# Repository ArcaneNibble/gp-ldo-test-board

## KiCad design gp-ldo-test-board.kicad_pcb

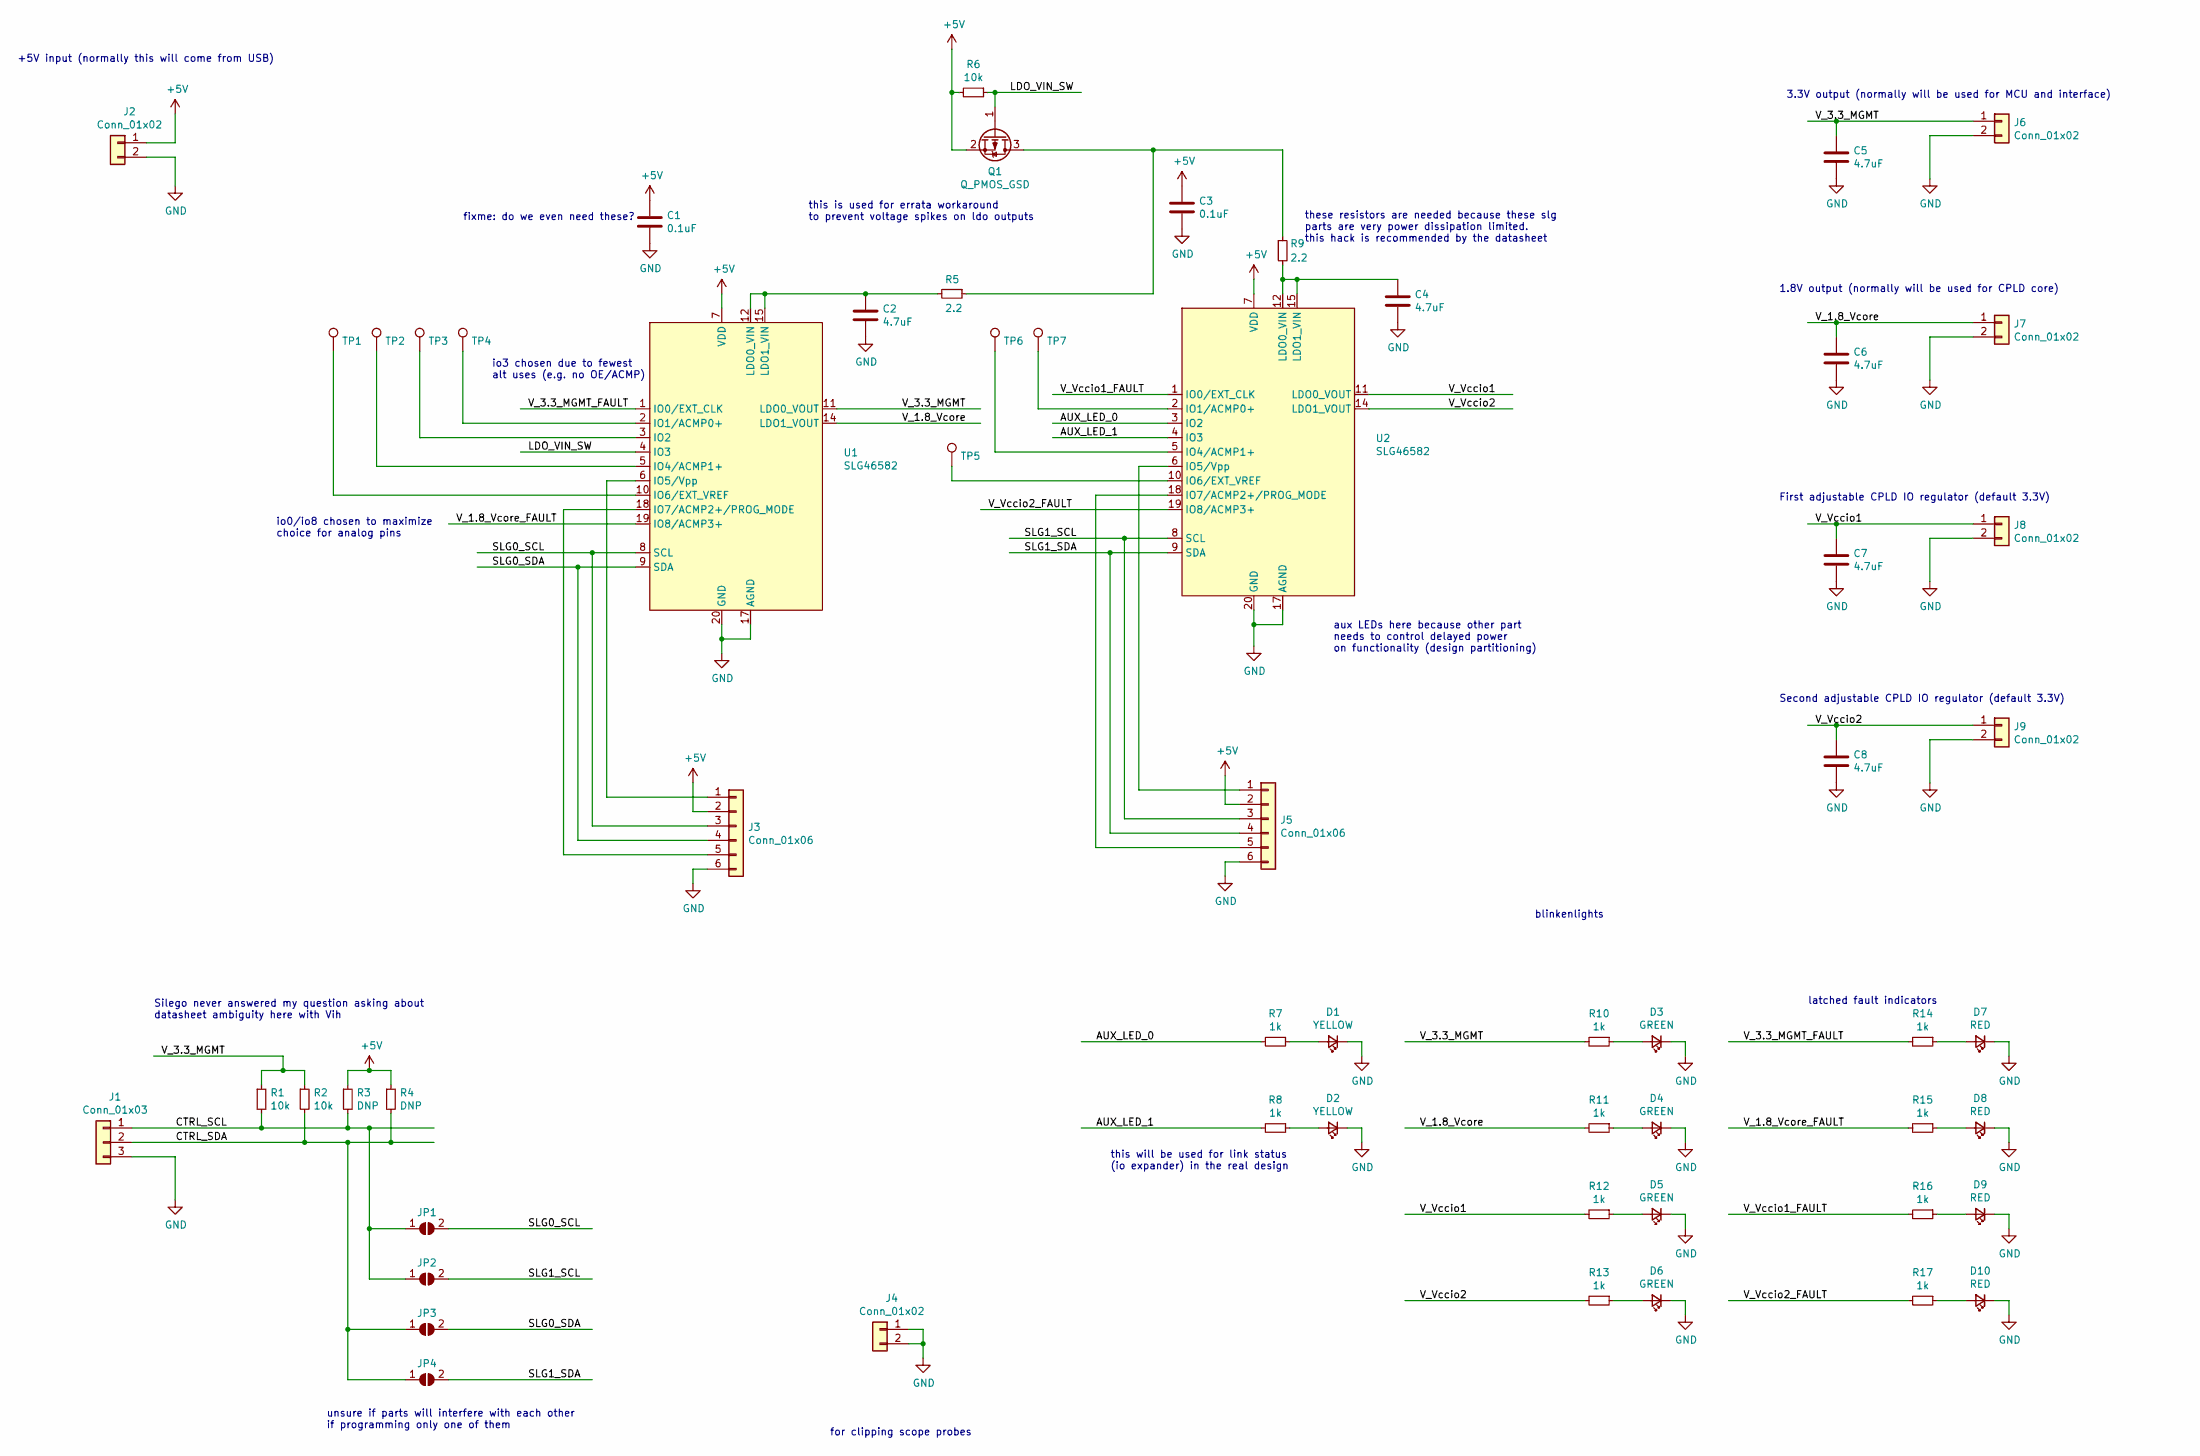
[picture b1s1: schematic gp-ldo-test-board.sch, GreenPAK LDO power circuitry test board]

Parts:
C1, C3: 0.1uF; C_0402_1005Metric
C2, C4, C5, C6, C7, C8: 4.7uF; C_0805_2012Metric
D1, D2: YELLOW; LED_0805_2012Metric
D3, D4, D5, D6: GREEN; LED_0805_2012Metric
D7, D8, D9, D10: RED; LED_0805_2012Metric
J1: Conn_01x03; PinHeader_1x03_P2.54mm_Vertical
J2, J4, J6, J7, J8, J9: Conn_01x02; PinHeader_1x02_P2.54mm_Vertical
J3, J5: Conn_01x06; PinHeader_1x06_P2.54mm_Vertical
JP1, JP2, JP3, JP4: SolderJumper_2_Open; SolderJumper-2_P1.3mm_Open_Pad1.0x1.5mm
Q1: Q_PMOS_GSD; SOT-23
R1, R2, R6: 10k; R_0402_1005Metric
R3, R4: DNP; R_0402_1005Metric
R5, R9: 2.2; R_0402_1005Metric
R7, R8, R10, R11, R12, R13, R14, R15, R16, R17: 1k; R_0402_1005Metric
TP1, TP2, TP3, TP4, TP5, TP6, TP7: TestPoint; TestPoint_Pad_1.0x1.0mm
U1, U2: SLG46582; SLG46580

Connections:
+5V: C1.1, C3.1, J2.1, J3.2, J5.2, Q1.2 (S), R3.1, R4.1, R6.2, U1.7 (VDD), U2.7 (VDD)
/AUX_LED_0: R7.2, U2.3 (IO2)
/AUX_LED_1: R8.2, U2.4 (IO3)
/CTRL_SCL: J1.1, JP1.1 (A), JP2.1 (A), R1.2, R3.2
/CTRL_SDA: J1.2, JP3.1 (A), JP4.1 (A), R2.2, R4.2
/LDO_VIN_SW: Q1.1 (G), R6.1, U1.4 (IO3)
/SLG0_SCL: J3.3, JP1.2 (B), U1.8 (SCL)
/SLG0_SDA: J3.4, JP3.2 (B), U1.9 (SDA)
/SLG1_SCL: J5.3, JP2.2 (B), U2.8 (SCL)
/SLG1_SDA: J5.4, JP4.2 (B), U2.9 (SDA)
/V_1.8_Vcore: C6.1, J7.1, R11.2, U1.14 (LDO1_VOUT), U1.16 (LDO1_VOUT)
/V_1.8_Vcore_FAULT: R15.2, U1.19 (IO8/ACMP3+)
/V_3.3_MGMT: C5.1, J6.1, R1.1, R2.1, R10.2, U1.11 (LDO0_VOUT), U1.13 (LDO0_VOUT)
/V_3.3_MGMT_FAULT: R14.2, U1.1 (IO0/EXT_CLK)
/V_Vccio1: C7.1, J8.1, R12.2, U2.11 (LDO0_VOUT), U2.13 (LDO0_VOUT)
/V_Vccio1_FAULT: R16.2, U2.1 (IO0/EXT_CLK)
/V_Vccio2: C8.1, J9.1, R13.2, U2.14 (LDO1_VOUT), U2.16 (LDO1_VOUT)
/V_Vccio2_FAULT: R17.2, U2.19 (IO8/ACMP3+)
GND: C1.2, C2.2, C3.2, C4.2, C5.2, C6.2, C7.2, C8.2, D1.1 (K), D2.1 (K), D3.1 (K), D4.1 (K), D5.1 (K), D6.1 (K), D7.1 (K), D8.1 (K), D9.1 (K), D10.1 (K), J1.3, J2.2, J3.6, J4.1, J4.2, J5.6, J6.2, J7.2, J8.2, J9.2, U1.17 (AGND), U1.20 (GND), U2.17 (AGND), U2.20 (GND)
unnamed: C2.1, R5.2, U1.12 (LDO0_VIN), U1.15 (LDO1_VIN)
unnamed: C4.1, R9.2, U2.12 (LDO0_VIN), U2.15 (LDO1_VIN)
unnamed: D1.2 (A), R7.1
unnamed: D2.2 (A), R8.1
unnamed: D3.2 (A), R10.1
unnamed: D4.2 (A), R11.1
unnamed: D5.2 (A), R12.1
unnamed: D6.2 (A), R13.1
unnamed: D7.2 (A), R14.1
unnamed: D8.2 (A), R15.1
unnamed: D9.2 (A), R16.1
unnamed: D10.2 (A), R17.1
unnamed: J3.1, U1.6 (IO5/Vpp)
unnamed: J3.5, U1.18 (IO7/ACMP2+/PROG_MODE)
unnamed: J5.1, U2.6 (IO5/Vpp)
unnamed: J5.5, U2.18 (IO7/ACMP2+/PROG_MODE)
unnamed: Q1.3 (D), R5.1, R9.1
unnamed: TP1.1, U1.10 (IO6/EXT_VREF)
unnamed: TP2.1, U1.5 (IO4/ACMP1+)
unnamed: TP3.1, U1.3 (IO2)
unnamed: TP4.1, U1.2 (IO1/ACMP0+)
unnamed: TP5.1, U2.10 (IO6/EXT_VREF)
unnamed: TP6.1, U2.5 (IO4/ACMP1+)
unnamed: TP7.1, U2.2 (IO1/ACMP0+)

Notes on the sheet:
+5V input (normally this will come from USB)
3.3V output (normally will be used for MCU and interface)
1.8V output (normally will be used for CPLD core)
First adjustable CPLD IO regulator (default 3.3V)
Second adjustable CPLD IO regulator (default 3.3V)
Silego never answered my question asking about datasheet ambiguity here with Vih
unsure if parts will interfere with each other if programming only one of them
this is used for errata workaround to prevent voltage spikes on ldo outputs
blinkenlights
io3 chosen due to fewest alt uses (e.g. no OE/ACMP)
io0/io8 chosen to maximize choice for analog pins
aux LEDs here because other part needs to control delayed power on functionality (design partitioning)
for clipping scope probes
this will be used for link status (io expander) in the real design
latched fault indicators
fixme: do we even need these?
these resistors are needed because these slg parts are very power dissipation limited. this hack is recommended by the datasheet

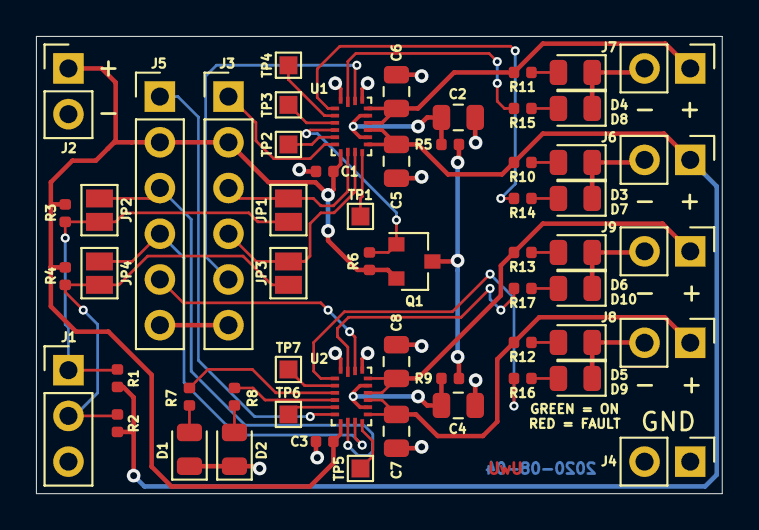
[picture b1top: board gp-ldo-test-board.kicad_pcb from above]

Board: 2 copper layers, 38.1 x 25.4 mm, 58 parts (0 on the bottom side), 43 nets.

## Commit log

2020-07-07 throw down some symbols
2020-07-07 initial schematic draft
2020-07-07 fix series resistors on ldos
2020-07-07 Commit draft1
2020-07-08 slg46580 library
2020-08-04 footprints and initial place
2020-08-04 initial route draft
2020-08-04 route major cleanup
2020-08-04 silk cleanup
2020-08-04 clean fab layer
2020-08-04 tweaks
2020-09-12 slg designs
